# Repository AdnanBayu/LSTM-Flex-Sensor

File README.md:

# SIBI Sign Language Recognition using Flex Sensor and LSTM Algorithm

> This repository implements a hand sign recognition system using flex sensor input, MQTT telemetry, and an LSTM-based prediction pipeline. The project was developed for the PKM-KC competition and as the author’s undergraduate final thesis project.

## Overview

- Collects gesture data from a flex sensor glove via MQTT.
- Uses an LSTM model to recognize alphabet letters from sequential sensor readings.
- Outputs recognized letters through audio playback.
- Includes data collection, configuration, prediction, and model files.

## Project structure

- `khadas/` - main Python source files for the real-time prediction program. This folder contains the application deployed on the Khadas VIM 4 single-board computer.
- `khadas/models/` - saved LSTM model definitions and weight files used by the Khadas program.
- `data/participant_*` - recorded sensor datasets for each participant.
- `config/` - calibration thresholds and configuration files used by the pipeline.
- `alphabet_audio/wav/` - audio files for alphabet pronunciation output.
- `Model Iteration Documentation/` - Jupyter notebooks, model experiments, and saved model checkpoints.

## Dependencies

Install the required Python packages before running the project.

```powershell
python -m pip install --upgrade pip
python -m pip install -r requirements.txt
```

> Note: `torch` installation may require a specific command depending on your CUDA support. If the generic install fails, visit https://pytorch.org/ and use the platform-specific install command.

## Usage

Run the main pipeline from the `khadas/` folder.

```powershell
cd khadas
python lstm_main.py --fn <mode> [options]
```

Available modes:

- `--fn loop_default` - print raw converted sensor payloads.
- `--fn config` - collect calibration values and save them to `config/<config_path>.txt`.
- `--fn get_data` - record gesture data to `data/<letter>-<id>.txt`.
- `--fn predict` - perform live LSTM prediction and optionally save results.

Examples:

```powershell
python lstm_main.py --fn config --config_path default
python lstm_main.py --fn get_data --letter a --id 1 --name user1 --seq_len 20
python lstm_main.py --fn predict --name session1 --model lstm
```

> Note: `khadas/audio.py` contains the audio playback helper class, but the main process is launched from `khadas/lstm_main.py`.

## Data and models

- Recorded sensor dataset is stored under `data/participant_*`.
- The default LSTM weight file is loaded from `khadas/models/LSTM/lstm_flex_best_model18.pth`.
- Calibration files are stored under `config/` and read by `khadas/lstm_tools.py`.
- Prediction results are saved to `result_lstm/<name>.txt`.

## Notes

- MQTT broker settings are configured in `khadas/mqtt.py`.
- Audio files are played from `alphabet_audio/wav/`.
- The LSTM prediction pipeline is implemented in `khadas/LSTM.py`.

## Non-technical documentation

- `PPT PKM-KC GLOVITOO.pptx` - competition pitching deck (Indonesian)
- `Progress Report.docx` - competition progress report (Indonesian)`

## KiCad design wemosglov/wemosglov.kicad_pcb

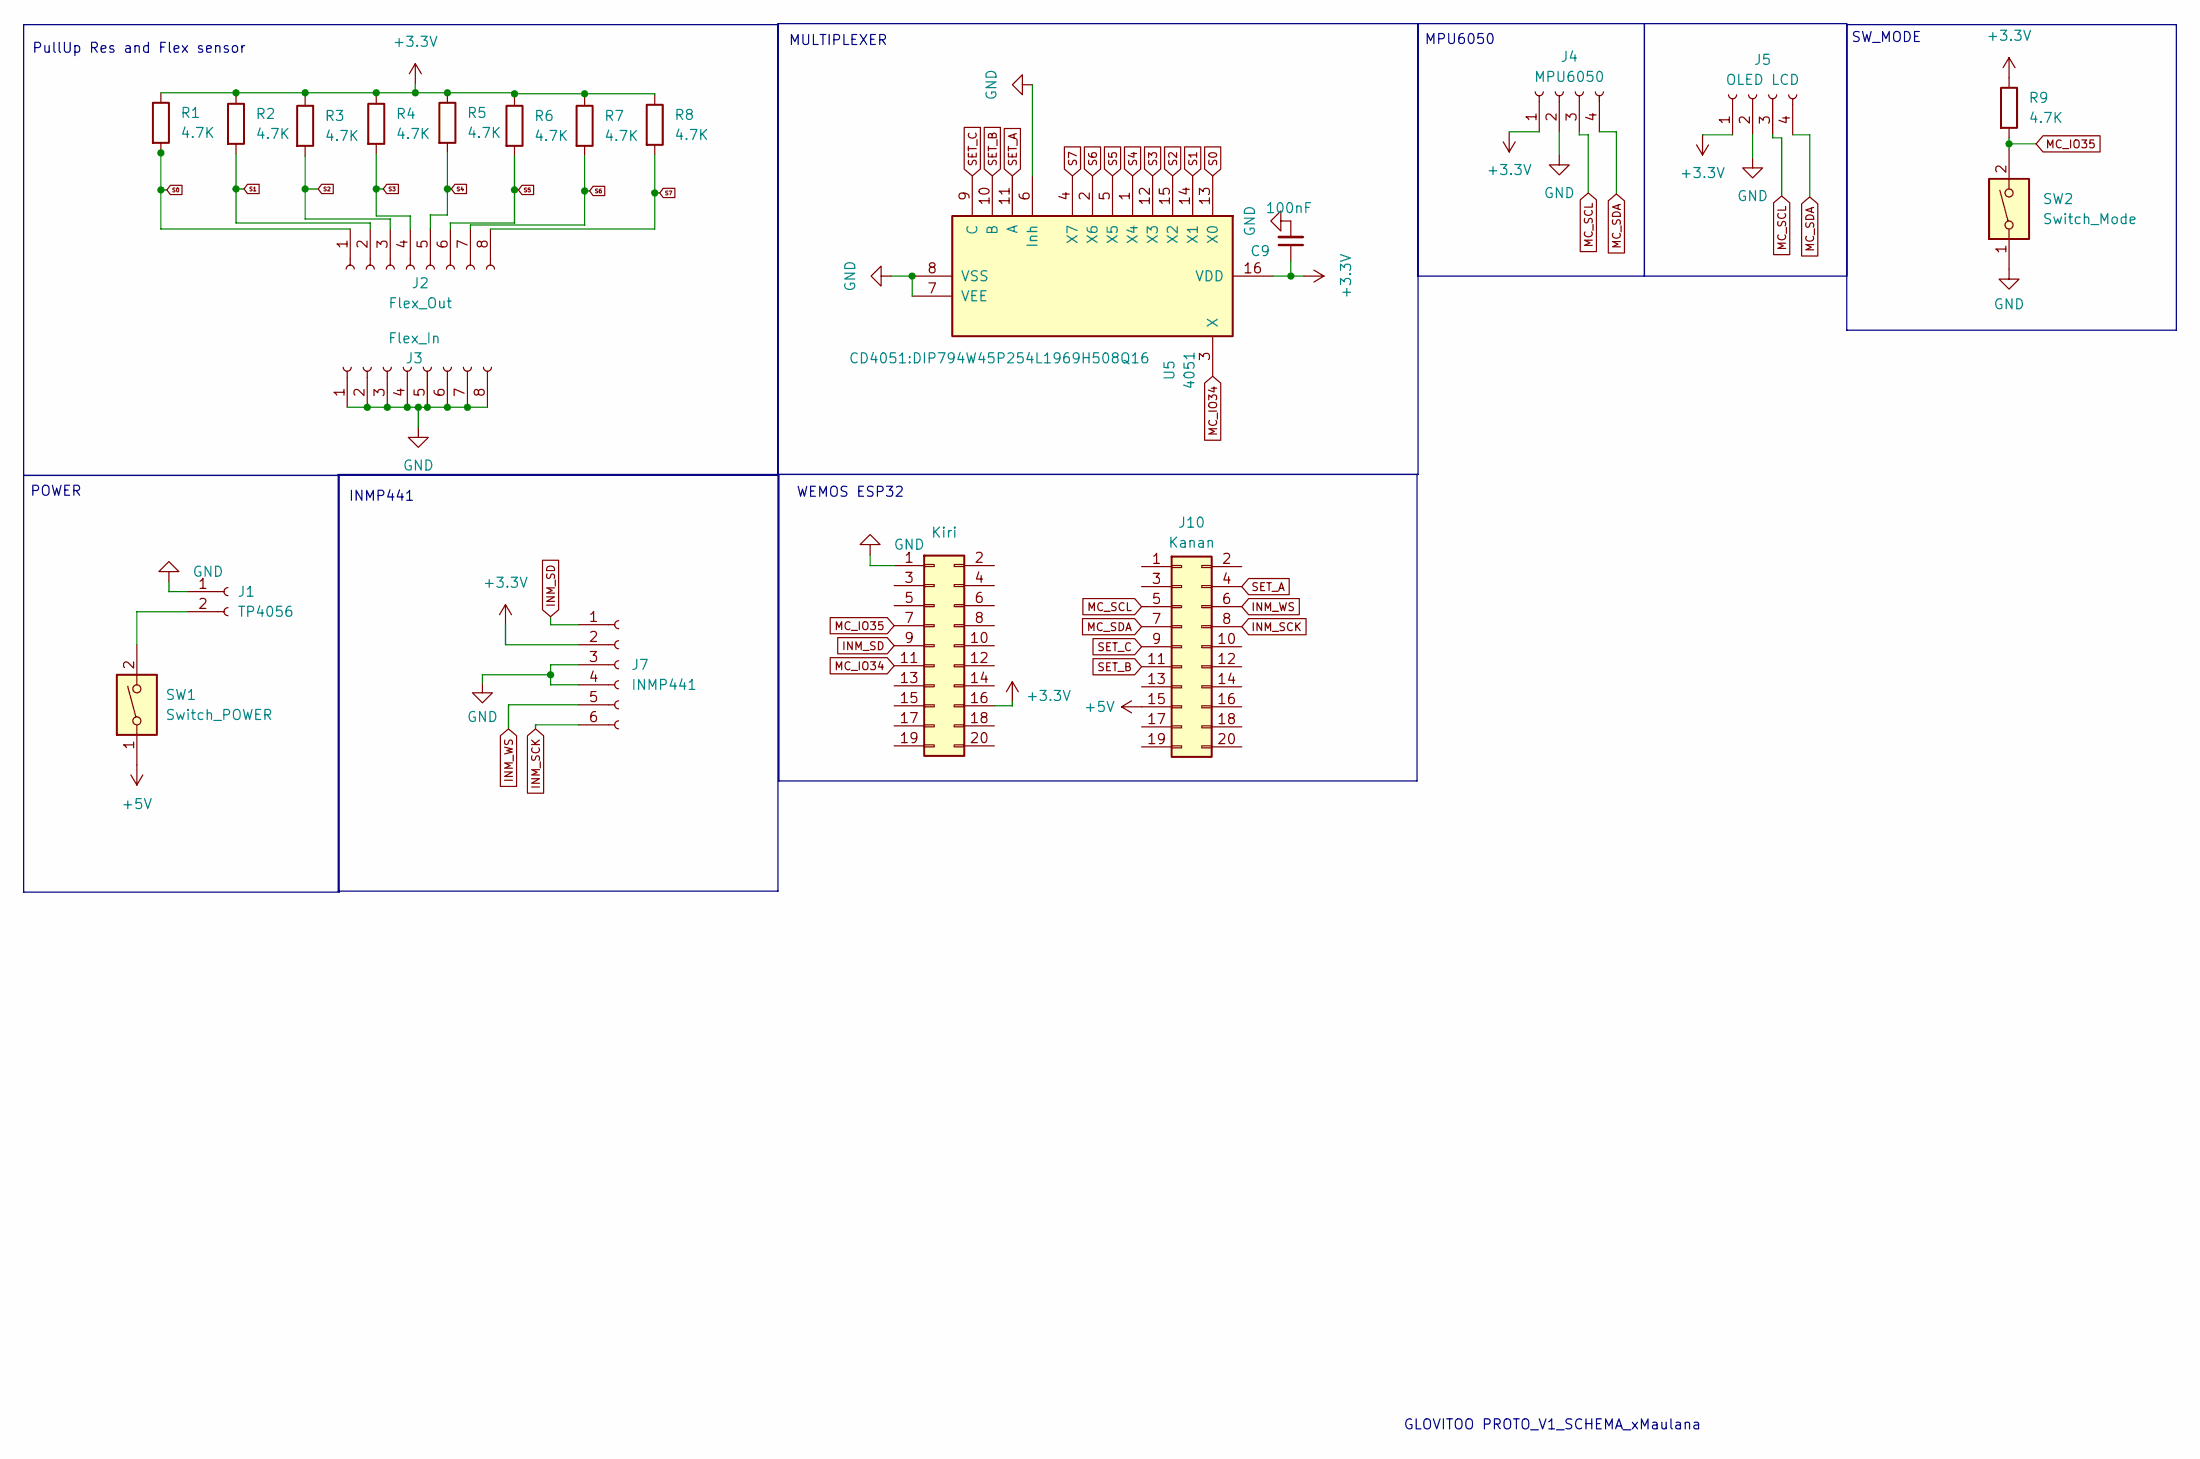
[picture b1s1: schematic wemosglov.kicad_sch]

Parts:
C9: 100nF; C_Disc_D9.0mm_W5.0mm_P5.00mm
J1: TP4056; PinHeader_1x02_P2.54mm_Vertical
J2: Flex_Out; PinHeader_1x08_P2.54mm_Vertical
J3: Flex_In; PinHeader_1x08_P2.54mm_Vertical
J4: MPU6050; PinHeader_1x04_P2.54mm_Vertical
J5: OLED LCD; PinHeader_1x04_P2.54mm_Vertical
J7: INMP441; PinHeader_1x06_P2.54mm_Vertical
J9: Kiri; PinHeader_2x10_P2.54mm_Vertical
J10: Kanan; PinHeader_2x10_P2.54mm_Vertical
R1, R2, R3, R4, R5, R6, R7, R8, R9: 4.7K; R_Axial_DIN0204_L3.6mm_D1.6mm_P5.08mm_Horizontal
SW1: Switch_POWER; SW_DIP_SPSTx01_Slide_9.78x4.72mm_W7.62mm_P2.54mm
SW2: Switch_Mode; SW_DIP_SPSTx01_Slide_9.78x4.72mm_W7.62mm_P2.54mm
U5: 4051; DIP794W45P254L1969H508Q16

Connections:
+3.3V: C9.1, J4.1, J5.1, J7.2, J9.16, R1.1, R2.1, R3.1, R4.1, R5.1, R6.1, R7.1, R8.1, R9.1, U5.16 (VDD)
+5V: J10.15, SW1.1
GND: C9.2, J1.1, J3.1, J3.2, J3.3, J3.4, J3.5, J3.6, J3.7, J3.8, J4.2, J5.2, J7.3, J7.4, J9.1, SW2.1, U5.6 (Inh), U5.7 (VEE), U5.8 (VSS)
INM_SCK: J7.6, J10.8
INM_SD: J7.1, J9.9
INM_WS: J7.5, J10.6
MC_IO34: J9.11, U5.3 (X)
MC_IO35: J9.7, R9.2, SW2.2
MC_SCL: J4.3, J5.3, J10.5
MC_SDA: J4.4, J5.4, J10.7
unnamed: J1.2, SW1.2
S0: J2.1, R1.2, U5.13 (X0)
S1: J2.2, R2.2, U5.14 (X1)
S2: J2.3, R3.2, U5.15 (X2)
S3: J2.4, R4.2, U5.12 (X3)
S4: J2.5, R5.2, U5.1 (X4)
S5: J2.6, R6.2, U5.5 (X5)
S6: J2.7, R7.2, U5.2 (X6)
S7: J2.8, R8.2, U5.4 (X7)
SET_A: J10.4, U5.11 (A)
SET_B: J10.11, U5.10 (B)
SET_C: J10.9, U5.9 (C)

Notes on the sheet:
GLOVITOO PROTO_V1_SCHEMA_xMaulana
MPU6050
SW_MODE
WEMOS ESP32
INMP441
POWER
PullUp Res and Flex sensor
MULTIPLEXER

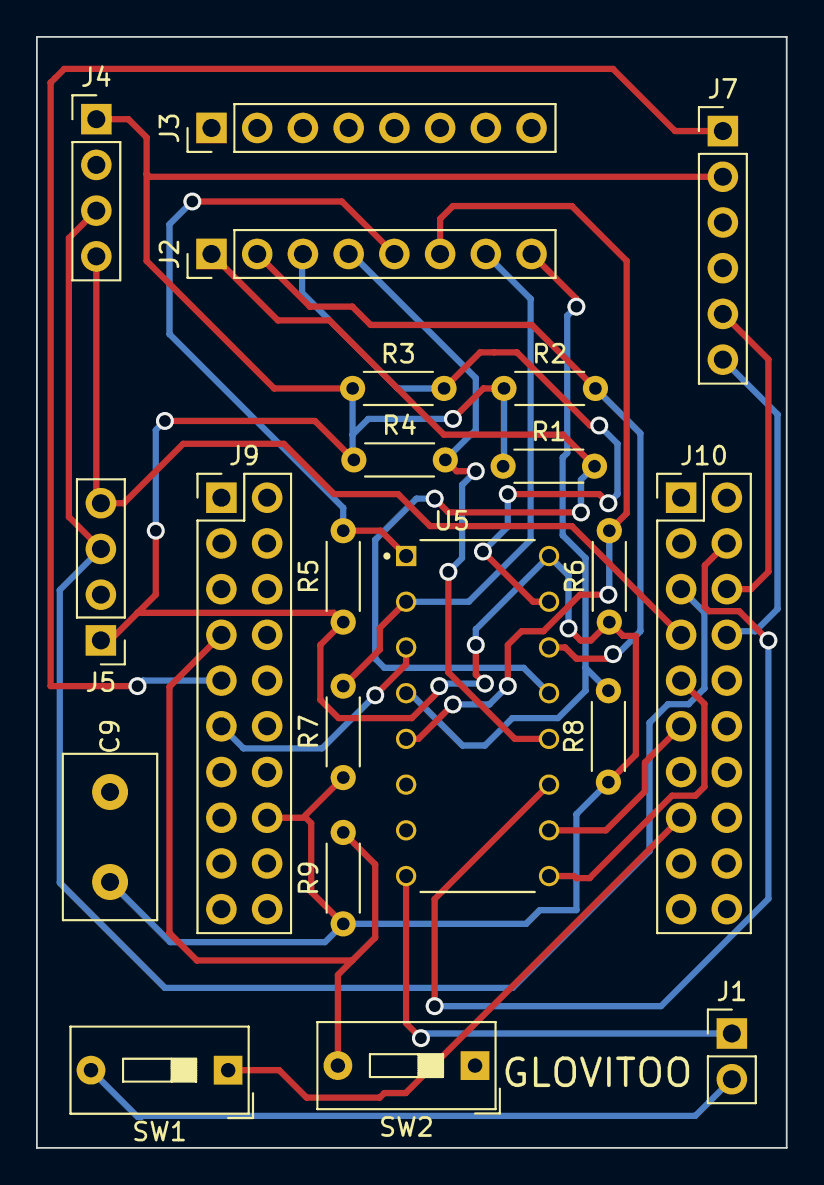
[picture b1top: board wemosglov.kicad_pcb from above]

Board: 2 copper layers, 41.7 x 61.7 mm, 21 parts (0 on the bottom side), 22 nets.

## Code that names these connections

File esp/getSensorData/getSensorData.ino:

#include <WiFi.h>
#include <MQTT.h>
#include <Mux.h>

#include <Adafruit_MPU6050.h>
#include <Adafruit_Sensor.h>

const char SSID[] = "khadas_ap";
const char PASS[] = "gluvitu321";
const int WIFI_TIMEOUT = 20000; //ms

#define oled_add 0x3C
#define SET_A 27
#define SET_B 16
#define SET_C 17
#define SEN_IN 34

WiFiClient net;
MQTTClient client;

unsigned long lastMillis = 0, lastSensorSend=0;

Adafruit_MPU6050 mpu;
admux::Mux glove(admux::Pin(SEN_IN, INPUT, admux::PinType::Analog), admux::Pinset(SET_A, SET_B, SET_C));


String allSensor(){
  sensors_event_t a,g,temp;
  float yaw, pitch;
  mpu.getEvent(&a, &g, &temp);
  String data = "";

  for(byte i=0; i<glove.channelCount();i++){
    data += String(glove.read(i)) + ",";
  }

  data += String(a.acceleration.x) + ",";
  data += String(a.acceleration.y) + ",";
  data += String(a.acceleration.z) + ",";

  data += String(g.gyro.x) + ",";
  data += String(g.gyro.y) + ",";
  data += String(g.gyro.z) + "\n";
  
  return data;
}

void connect(){
  Serial.print("Connecting");
  while (WiFi.status() != WL_CONNECTED) {
    Serial.print(".");
    delay(500);
  }

  while (!client.connect("glovitoo-esp32", "acumalaka", "aezakmi123")) {
    Serial.print(".");
    delay(500);
  }

  
  client.subscribe("glovitoo/subtester");
  client.subscribe("glovitoo/speech");
}

void setup() {
  Serial.begin(115200);

  //MPU sensor
  Serial.println("Beginning MPU");
  if (!mpu.begin()) {
    Serial.println("Sensor init failed");
    while (1)
      yield();
  }
  delay(1000);
  ////////////////////////////////

  //WIFI&MQTT
  Serial.println("Begin WIFI and MQTT");
  WiFi.begin(SSID, PASS);

  client.begin("10.42.0.1", net);
  client.onMessage(messageReceived);

  connect();

}

void loop() {
  if((millis() - lastMillis) >10){
    client.loop();
    if (!client.connected()) {
      connect();
    }

    if((millis() - lastSensorSend) > 50){
      client.publish("glovitoo/sensors", allSensor());
      lastSensorSend=millis();
    }

    lastMillis = millis();
  }

}


void messageReceived(String &topic, String &payload){
  Serial.println("Payload masuk dari topik: " + topic + " dengan payload: " + payload);
}

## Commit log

2025-01-09 add schematics and edit folder&file name
2025-05-14 add google colab lstm flex sensor
2025-05-14 add google colab lstm flex imu
2025-05-24 Tensorflow LSTM model for system using flex sensor
2025-05-24 Tensorflow LSTM model for system using flex sensor and IMU sensor
2025-06-13 added pytorch model and finishing pipeline integration
2025-06-17 fixing model and pipeline integration
2025-06-17 fixing realtime pipeline integration
2025-06-17 fixing model and pipeline
2025-07-02 almost done all
2025-07-10 done
2025-07-12 Finished LSTM model training using sensor flex data
2025-07-12 Finished LSTM model training using sensor flex and IMU data
2025-07-12 added collab pytorch file and deleted several unnecessary document
2025-07-20 Created using Colab
2025-07-20 add average accuracy realtime test calculation function
2025-08-17 finished
    push commit after final thesis defense
2026-04-06 adjust documentation
